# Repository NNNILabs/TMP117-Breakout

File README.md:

# TMP117 Breakout
## Introduction
The TMP117 from Texas Instruments is a precision temperature sensor that has a stated accurace that rivals Platinum RTDs. It senses temperature though an internal diode-connected PNP BJT, digitizes it using an internal ADC and communicates with an external controller through I2C. An accuracy of +/-0.1C is claimed over a -55C to +145C temperature range. 
## Project Motivation
I wanted to be able to use the TMP117 for various projects without separately laying out a circuit on each PCB. This breakout board makes it easy to use with regular 2.54mm pitch pin headers. It can also be placed directly on a PCB through the castellations.
## Usage
The board is populated and connected to an external controller through the breakout pins/castellations. The TMP117 uses a 16-bit two's complement format. 
## List of Files
- Hardware: Schematic and PCB KiCAD files, GERBER files

- Software: Example code using Raspberry Pi Pico (PIO and hardware I2C)
- Resources: 
## Application Examples
## Notes
## Links
- Datasheet: https://www.ti.com/lit/ds/symlink/tmp117.pdf

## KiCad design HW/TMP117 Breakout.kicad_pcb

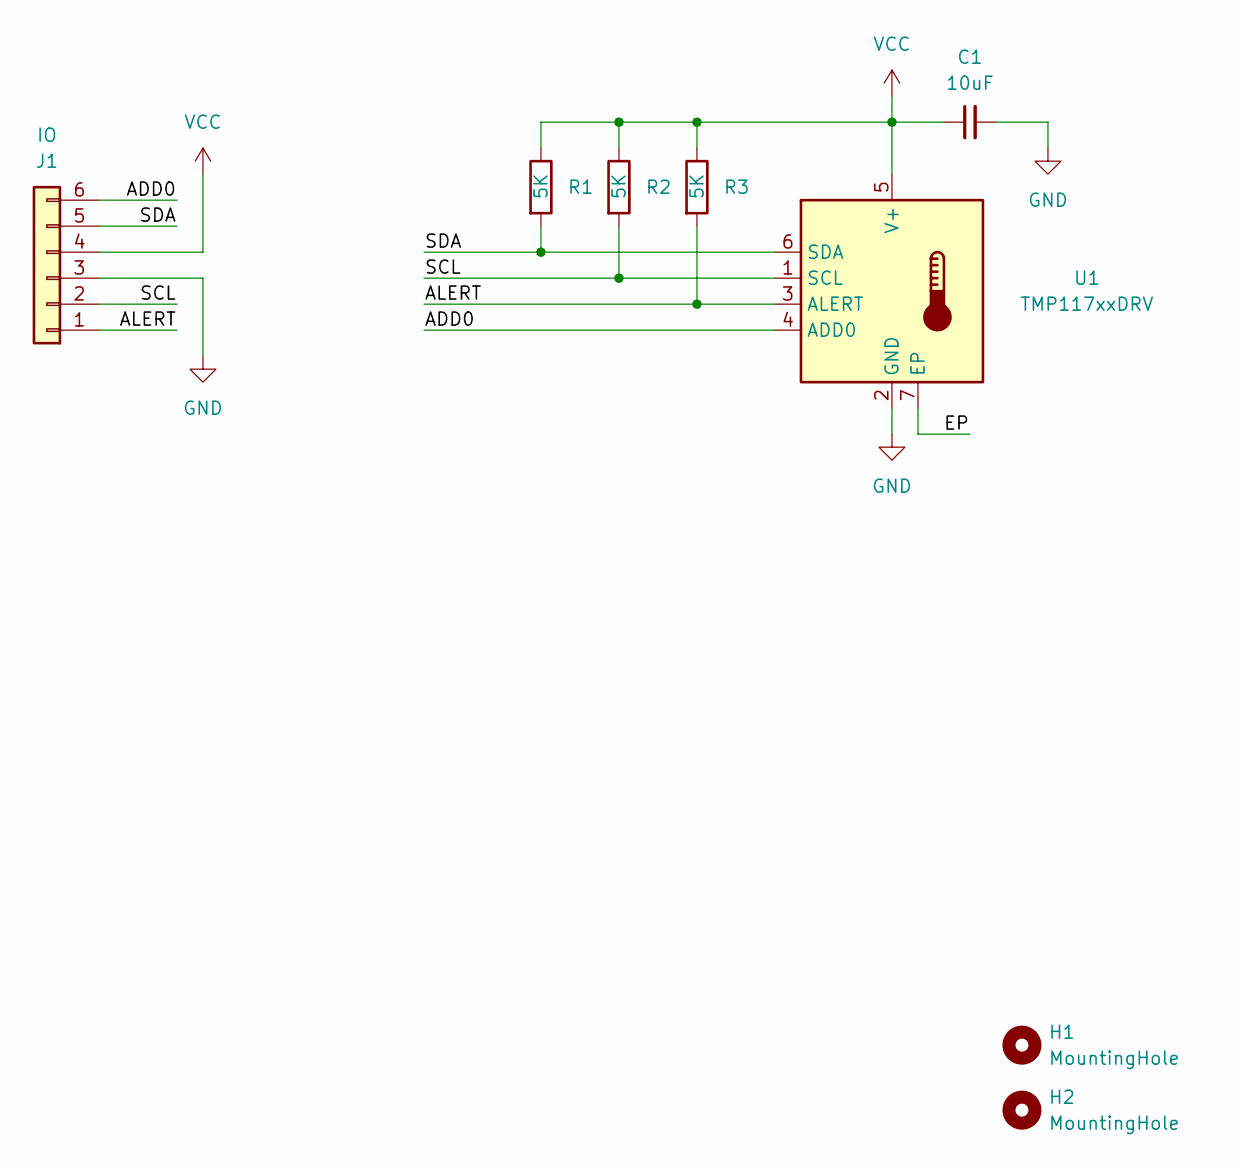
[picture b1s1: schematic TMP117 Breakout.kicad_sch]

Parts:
C1: 10uF; C_0603_1608Metric
H1, H2: MountingHole; MountingHole_3.2mm_M3_Pad_Via
J1: IO; PinHeader_1x06_P2.54mm_Vertical
R1, R2, R3: 5K; R_0603_1608Metric
U1: TMP117xxDRV; WSON-6-1EP_2x2mm_P0.65mm_EP1x1.6mm

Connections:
/ADD0: J1.6, U1.4 (ADD0)
/ALERT: J1.1, R3.2, U1.3 (ALERT)
/EP: U1.7 (EP)
/SCL: J1.2, R2.2, U1.1 (SCL)
/SDA: J1.5, R1.2, U1.6 (SDA)
GND: C1.2, J1.3, U1.2 (GND)
VCC: C1.1, J1.4, R1.1, R2.1, R3.1, U1.5 (V+)

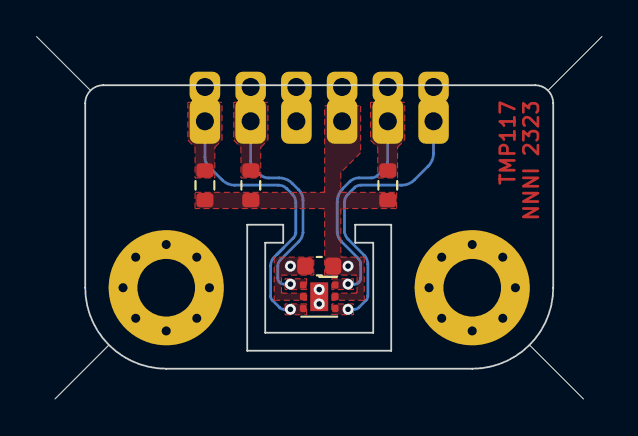
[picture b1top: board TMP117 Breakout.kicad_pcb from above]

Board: 2 copper layers, 26.0 x 15.8 mm, 8 parts (0 on the bottom side), 6 nets.

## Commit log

2023-06-04 Preliminary PCB Layout
    Added TMP117 and surrounding parts, completed preliminary layout and routing.
2023-06-10 Completed layout
    - Completed PCB layout and routing
    - Plotted GERBER files
2023-06-10 Updated files
    - Added NNNI branding
    - Updated traces to regions
    - Updated Image
    - Reexported GERBER files
2023-06-19 Updated files
